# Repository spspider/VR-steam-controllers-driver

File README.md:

# VR-Driver Project

A custom VR controller driver for SteamVR that receives UDP data from external controllers (Arduino-based or mobile devices) and translates it into VR controller input.

## Quick Start

### Prerequisites

1. **Install ALVR** - Download from [ALVR GitHub Releases](https://github.com/alvr-org/ALVR/releases)
2. **Install PhoneVR** - Use ALVR-compatible version from [PhoneVR](https://phonevr.app/)
3. **SteamVR** - Install via Steam

### Installation

## YOU HAVE DIFFERENT OPTIONS HOW TO RUN THIS USING DEVICES WHICH YOU HAVE
1. Using you own webcamera
2. Using your Android phone

#### Option 1: Use Pre-built Release (Recommended)
1. Download the latest release from [Releases](../../releases)
2. Extract files to a temporary folder
3. Run `manual_install.bat` as Administrator
4. Follow the testing steps below

#### Option 2: Manual Installation
1. Copy driver files to SteamVR drivers folder:
   ```
   C:\Program Files (x86)\Steam\steamapps\common\SteamVR\drivers\cvdriver\
   ```
2. Create folder structure:
   ```
   cvdriver/
   ├── bin/win64/
   │   ├── driver_cvdriver.dll
   │   └── openvr_api.dll
   └── resources/
       ├── driver.vrdrivermanifest
       └── input/
           └── cvcontroller_profile.json
   ```
3. Register driver in `openvrpaths.vrpath`:
   ```
   C:\Users\<YourName>\AppData\Local\openvr\openvrpaths.vrpath
   ```
   Add:
   ```json
   {
     "external_drivers": [
       "C:\\Program Files (x86)\\Steam\\steamapps\\common\\SteamVR\\drivers\\cvdriver"
     ]
   }
   ```

### Testing the Installation

1. **Test UDP Communication:**
   ```bash
   cd steamVR-controller-driver-C
   python simple_simulator.py
   ```

2. **Start SteamVR** and check for 2 controllers (CV_Controller_Left, CV_Controller_Right)

3. **Verify in SteamVR Status** → Devices → Manage Controllers

## Hardware Setup

### PCB Design
The project includes a custom PCB design for the VR controller hardware.

### Ordering PCB
1. **PCB Manufacturer:** [PCBWay](https://www.pcbway.com/)
2. **Gerber Files:** Located in `kicad/gerber/gerber.zip`
3. **Assembly Guide:** See `kicad/smd-placement.pdf`
4. **Print Dimensions:** See `kicad/print_scheme_sizes.pdf`

## ArUco Marker Generation

The project uses ArUco markers for visual tracking. Generate markers using:

```bash
cd Android_ArCode/python-test
pip install -r requirements.txt
python generate_aruco.py
```

This creates markers `aruco_marker_0.png` through `aruco_marker_9.png`.

### ArUco Code Reference
- **Print Template:** `kicad/scheme-print-arUco-code.pdf`
- **Dictionary:** DICT_6X6_250
- **Marker Size:** 300x300 pixels with 20px border

## How It Works

The VR driver operates as a UDP server that:

1. **Listens** for UDP packets on port 5555 (configurable)
2. **Receives** controller data including:
   - Quaternion orientation (w, x, y, z)
   - Accelerometer data (x, y, z)
   - Gyroscope data (x, y, z)
   - Button states (16-bit mask)
   - Trigger values (0-255)
3. **Translates** this data into SteamVR controller input
4. **Updates** controller positions and states in real-time

### Data Packet Format
```c
struct ControllerData {
    uint8_t controller_id;    // 0 = left, 1 = right
    uint32_t packet_number;   // Sequence number
    float quat[4];           // Orientation (w,x,y,z)
    float accel[3];          // Acceleration (x,y,z)
    float gyro[3];           // Angular velocity (x,y,z)
    uint16_t buttons;        // Button bitmask
    uint8_t trigger;         // Trigger value 0-255
    uint8_t checksum;        // Data integrity check
};
```

## Python Testing Scripts

### Controller Simulator
```bash
python steamVR-controller-driver-C/simple_simulator.py
```
Simulates 2 VR controllers with rotating motion and button presses.

### UDP Test Server
```bash
python Android_ArCode/python-test/test_server.py
```
Receives and displays UDP packets for debugging.

## Android ArUco Tracking

The `Android_ArCode` folder contains an Android application that:
- Uses camera to detect ArUco markers
- Calculates controller position/orientation
- Sends UDP data to the VR driver

### Building Android App
```bash
cd Android_ArCode
./gradlew assembleDebug
```

## Project Documentation

### Technical References
- **PCB Assembly:** `kicad/smd-placement.pdf`
- **ArUco Printing:** `kicad/scheme-print-arUco-code.pdf`
- **Board Dimensions:** `kicad/print_scheme_sizes.pdf`

### Driver Documentation
- **Setup Guide:** `steamVR-controller-driver-C/README.md`
- **Testing Guide:** `steamVR-controller-driver-C/TESTING_GUIDE.md`
- **Step-by-Step:** `steamVR-controller-driver-C/STEP_BY_STEP_TESTING.md`

## Troubleshooting

### Controllers Not Appearing
1. Check SteamVR logs: `C:\Program Files (x86)\Steam\logs\vrserver.txt`
2. Verify driver registration in `openvrpaths.vrpath`
3. Ensure UDP port 5555 is not blocked by firewall

### No UDP Data Received
1. Test with `simple_simulator.py`
2. Check firewall settings
3. Verify IP address and port configuration

### Build Issues
1. Ensure OpenVR SDK is properly installed
2. Check CMake configuration
3. Verify Visual Studio 2022 is installed

## Links and Resources

- **ALVR:** [GitHub](https://github.com/alvr-org/ALVR) | [Releases](https://github.com/alvr-org/ALVR/releases)
- **PhoneVR:** [Official Site](https://phonevr.app/)
- **PCBWay:** [PCB Manufacturing](https://www.pcbway.com/)
- **OpenVR:** [Valve OpenVR SDK](https://github.com/ValveSoftware/openvr)
- **SteamVR:** [Steam Store](https://store.steampowered.com/app/250820/SteamVR/)

## Project Structure

```
VR-Driver/
├── Android_ArCode/              # Android ArUco tracking app
│   └── python-test/            # Python test scripts
├── kicad/                      # PCB design files
│   ├── gerber/                # Manufacturing files
│   └── images/                # PCB photos
├── steamVR-controller-driver-C/ # Main VR driver
│   ├── src/                   # Driver source code
│   ├── resources/             # Driver manifest and profiles
│   └── manual_install.bat     # Installation script
└── README.md                  # This file
```

## License

This project is open source. Check individual component licenses for specific terms.

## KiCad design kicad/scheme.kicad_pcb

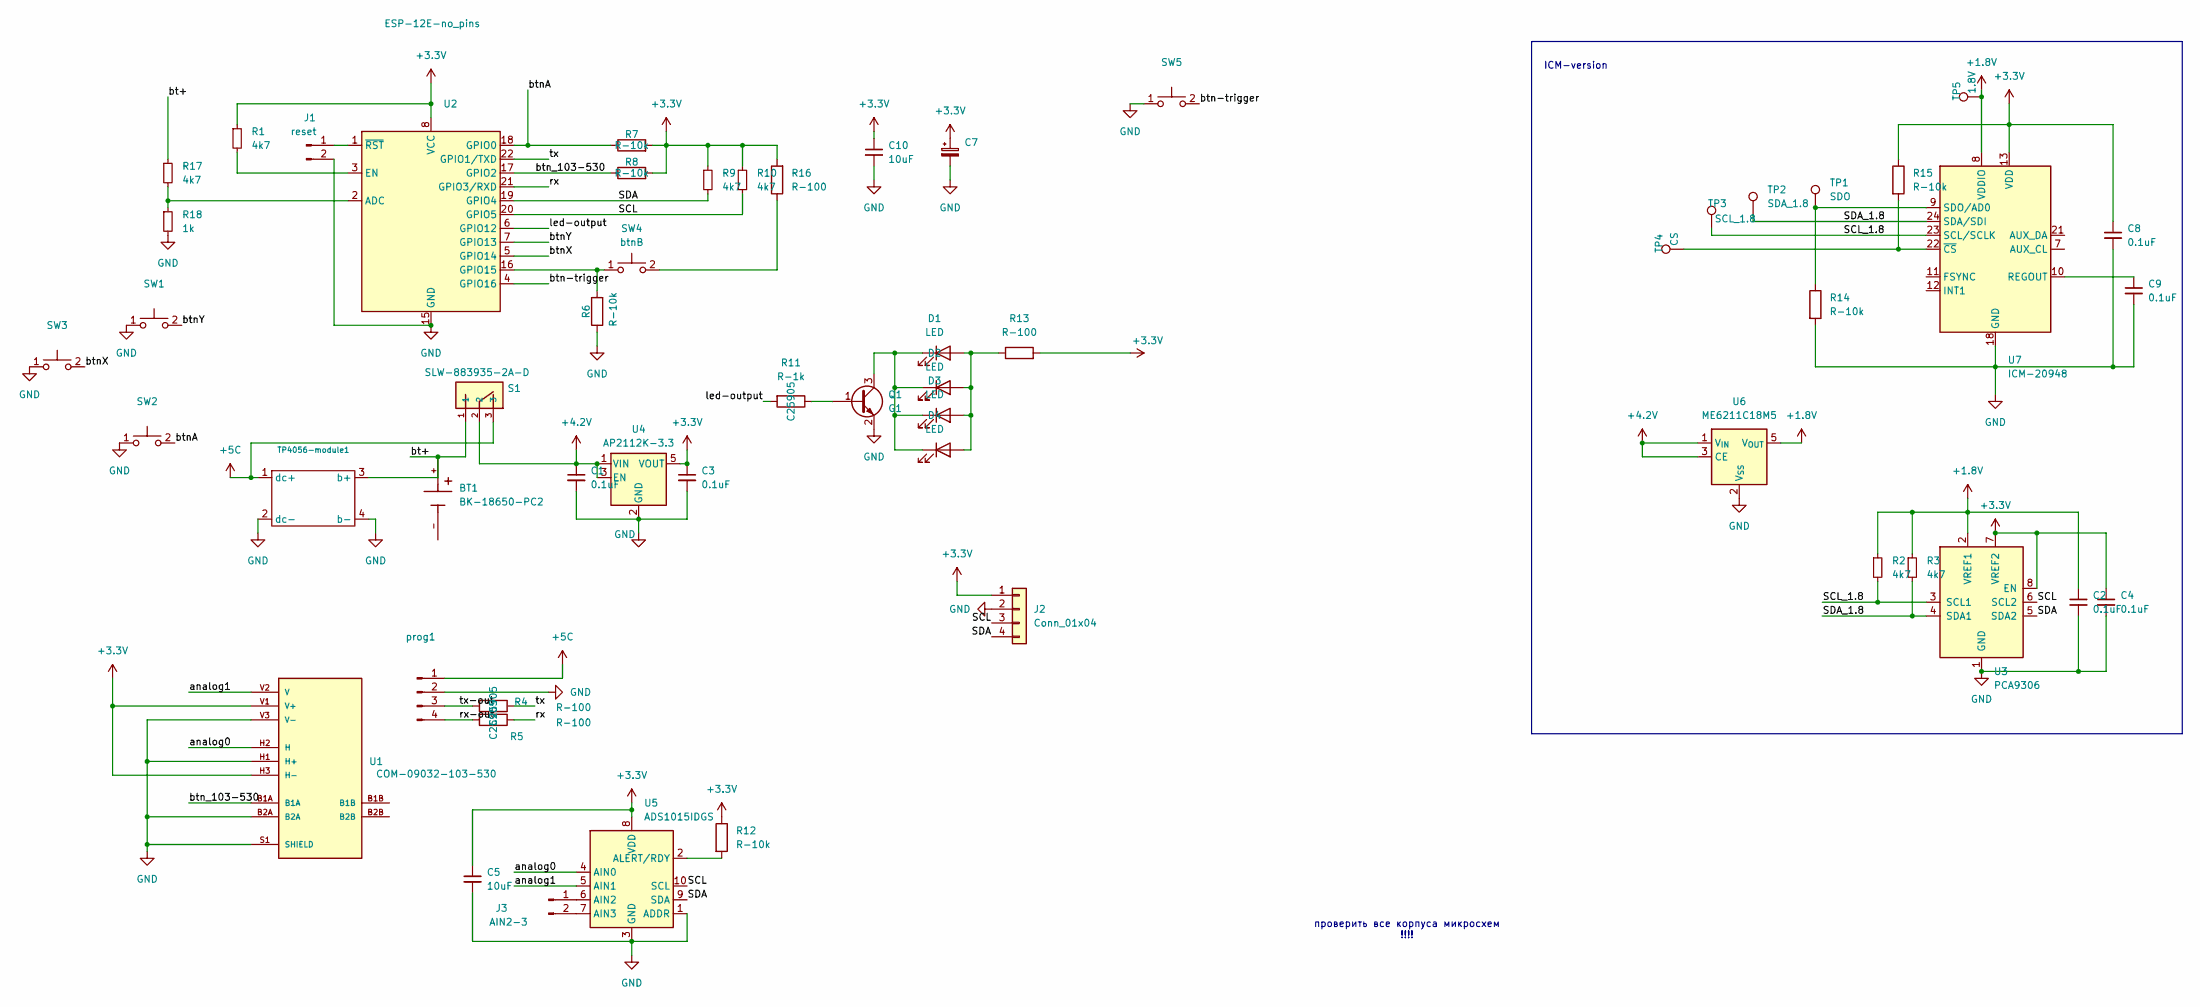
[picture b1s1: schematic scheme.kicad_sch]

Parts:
BT1: BK-18650-PC2; BAT_BK-18650-PC2-battery-holder; PARTREV F
C1, C2, C3, C4, C7, C8, C9: 0.1uF; R_0805_2012Metric_Pad1.20x1.40mm_HandSolder
C5, C10: 10uF; R_0805_2012Metric_Pad1.20x1.40mm_HandSolder
D1, D2, D3, D4: LED; LED_D5.0mm
J1: reset; PinHeader_2x01_P2.54mm_Vertical
J2: Conn_01x04; PinSocket_1x04_P2.54mm_Vertical
J3: AIN2-3; PinHeader_2x01_P2.54mm_Vertical
Q1: G1; SOT-23; LCSC Part C2145
R1, R2, R3, R9, R10, R17: 4k7; R_0805_2012Metric_Pad1.20x1.40mm_HandSolder
R4, R5: R-100; R_0805_2012Metric_Pad1.20x1.40mm_HandSolder; LCSC Part C25905
R6, R7, R8: R-10k; R_0805_2012Metric_Pad1.20x1.40mm_HandSolder; LCSC Part C17414
R11: R-1k; R_0805_2012Metric_Pad1.20x1.40mm_HandSolder; LCSC Part C25905
R12, R14, R15: R-10k; R_0805_2012Metric_Pad1.20x1.40mm_HandSolder; JLCPCB Part C17414
R13, R16: R-100; R_0805_2012Metric_Pad1.20x1.40mm_HandSolder; JLCPCB Part C17414
R18: 1k; R_0805_2012Metric_Pad1.20x1.40mm_HandSolder
S1: SLW-883935-2A-D; SW_OS102011MS2QN1_slideSwitch; PARTREV 1.01
SW1, SW2, SW3, SW5: SW_PUSH_6mm_H4.3mm
SW4: btnB; SW_PUSH_6mm_H4.3mm
TP1: SDO; TestPoint_Pad_1.0x1.0mm
TP2: SDA_1.8; TestPoint_Pad_1.0x1.0mm
TP3: SCL_1.8; TestPoint_Pad_1.0x1.0mm
TP4: CS; TestPoint_Pad_1.0x1.0mm
TP5: 1.8V; TestPoint_Pad_1.0x1.0mm
TP4056-module1: TP4056-short
U1: COM-09032-103-530; XDCR_COM-09032-103-530; PARTREV N/A
U2: ESP-12E-no_pins; ESP-12E_no_pins
U3: PCA9306; MSOP-8_3x3mm_P0.65mm
U4: AP2112K-3.3; SOT25
U5: ADS1015IDGS; VSSOP-10_3x3mm_P0.5mm
U6: ME6211C18M5; SOT-23-5
U7: ICM-20948; InvenSense_QFN-24_3x3mm_P0.4mm
prog1: prog; PinHeader_1x04_P2.54mm_Vertical

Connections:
+1.8V: C2.1, R2.1, R3.1, TP5.1, U3.2 (VREF1), U6.5 (V_{OUT}), U7.8 (VDDIO)
+3.3V: C3.1, C4.1, C5.1, C7.1, C8.1, C10.1, J2.1, R1.1, R7.2, R8.2, R9.1, R10.1, R12.1, R13.2, R15.1, R16.2, U1.H3 (H-), U1.V1 (V+), U2.8 (VCC), U3.7 (VREF2), U3.8 (EN), U4.5 (VOUT), U5.8 (VDD), U7.13 (VDD)
+4.2V: C1.1, S1.2, U4.1 (VIN), U4.3 (EN), U6.1 (V_{IN}), U6.3 (CE)
+5C: S1.3, TP4056-module1.1 (dc+), prog1.1
/SCL: J2.3, R10.2, U2.20 (GPIO5), U3.6 (SCL2), U5.10 (SCL)
/SCL_1.8: R2.2, TP3.1, U3.3 (SCL1), U7.23 (SCL/SCLK)
/SDA: J2.4, R9.2, U2.19 (GPIO4), U3.5 (SDA2), U5.9 (SDA)
/SDA_1.8: R3.2, TP2.1, U3.4 (SDA1), U7.24 (SDA/SDI)
/analog0: U1.H2 (H), U5.4 (AIN0)
/analog1: U1.V2 (V), U5.5 (AIN1)
/bt+: BT1.+, R17.1, S1.1, TP4056-module1.3 (b+)
/btn-trigger: SW5.2 (D), U2.4 (GPIO16)
/btnA: R7.1, SW2.2 (D), U2.18 (GPIO0)
/btnX: SW3.2 (D), U2.5 (GPIO14)
/btnY: SW1.2 (D), U2.7 (GPIO13)
/btn_103-530: R8.1, U1.B1A, U2.17 (GPIO2)
/led-output: R11.2, U2.6 (GPIO12)
/rx: R5.1, U2.21 (GPIO3/RXD)
/rx-out: R5.2, prog1.4
/tx: R4.1, U2.22 (GPIO1/TXD)
/tx-out: R4.2, prog1.3
GND: C1.2, C2.2, C3.2, C4.2, C5.2, C7.2, C8.2, C9.2, C10.2, J1.2, J2.2, Q1.2 (E), R6.1, R14.2, R18.2, SW1.1 (C), SW2.1 (C), SW3.1 (C), SW5.1 (C), TP4056-module1.2 (dc-), TP4056-module1.4 (b-), U1.B2A, U1.H1 (H+), U1.S1 (SHIELD), U1.V3 (V-), U2.15 (GND), U3.1 (GND), U4.2 (GND), U5.1 (ADDR), U5.3 (GND), U6.2 (V_{SS}), U7.18 (GND), U7.20 (GND), prog1.2
unnamed: D1.2 (A), D2.2 (A), D3.2 (A), D4.2 (A), R13.1
unnamed: D1.1 (K), D2.1 (K), D3.1 (K), D4.1 (K), Q1.3 (C)
unnamed: J1.1, U2.1 (~RST)
unnamed: J3.1, U5.6 (AIN2)
unnamed: J3.2, U5.7 (AIN3)
unnamed: Q1.1 (B), R11.1
unnamed: R6.2, SW4.1 (C), U2.16 (GPIO15)
unnamed: R16.1, SW4.2 (D)
unnamed: R17.2, R18.1, U2.2 (ADC)
unnamed: R1.2, U2.3 (EN)
unnamed: R12.2, U5.2 (ALERT/RDY)
unnamed: C9.1, U7.10 (REGOUT)
unnamed: R14.1, TP1.1, U7.9 (SDO/AD0)
unnamed: R15.2, TP4.1, U7.22 (~CS)

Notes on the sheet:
проверить все корпуса микросхем !!!!
ICM-version

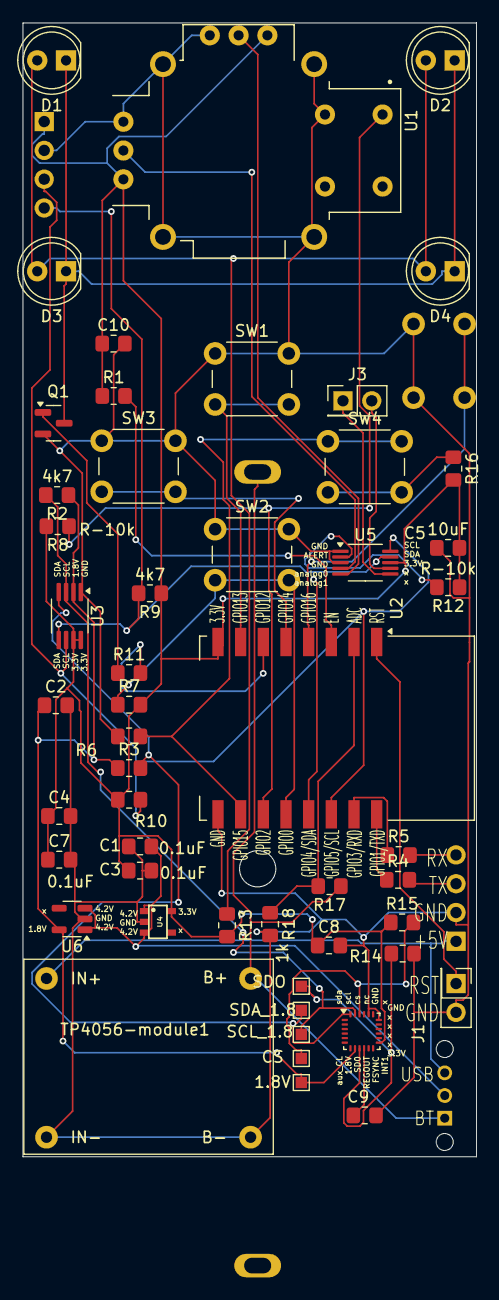
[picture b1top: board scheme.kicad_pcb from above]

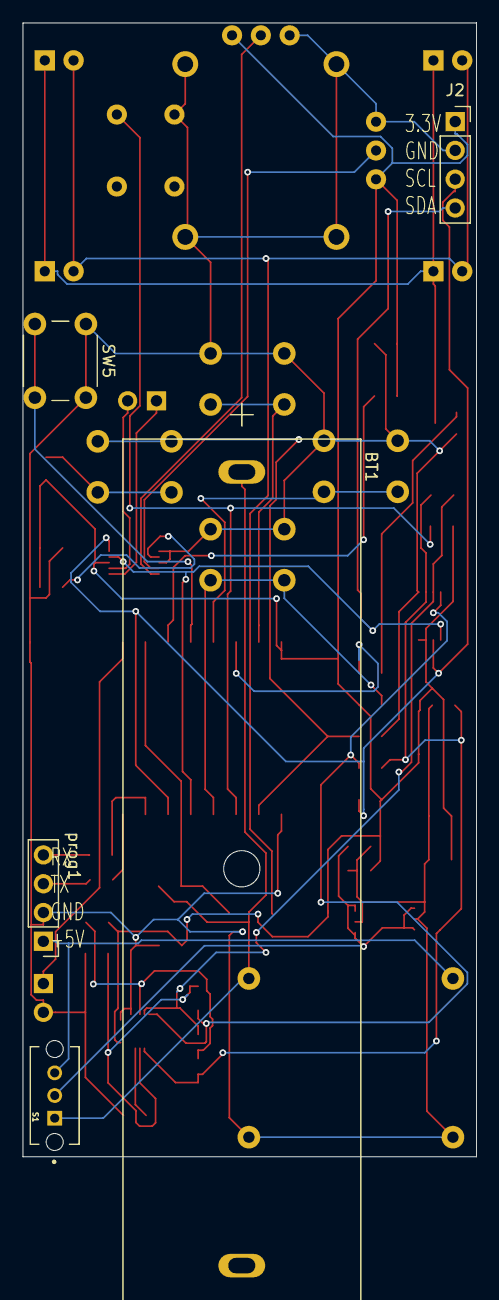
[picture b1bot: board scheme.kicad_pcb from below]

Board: 2 copper layers, 40.0 x 100.0 mm, 56 parts (5 on the bottom side), 36 nets.

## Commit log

2026-01-02 working with opencv android
2026-01-02 additional code
2026-01-04 renamed
2026-01-04 working arduino controllers!!!!
2026-01-05 vr-driver-working
2026-01-05 kicad-updates
2026-01-05 changes in scheme
2026-01-07 added Readme
2026-01-07 aruco tracking and calibration fixed
2026-01-07 arUco code for android, android working with controllers
2026-01-09 udpate in scheme
2026-01-27 Gyro mouse filter
2026-02-01 simmulator HMD not working, autocalibration
2026-02-01 multi-source support, android camera scale fix
2026-02-01 gamepad controller
